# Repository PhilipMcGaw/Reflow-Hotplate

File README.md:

# reflow_hotplate
 SMD reflow hot plate

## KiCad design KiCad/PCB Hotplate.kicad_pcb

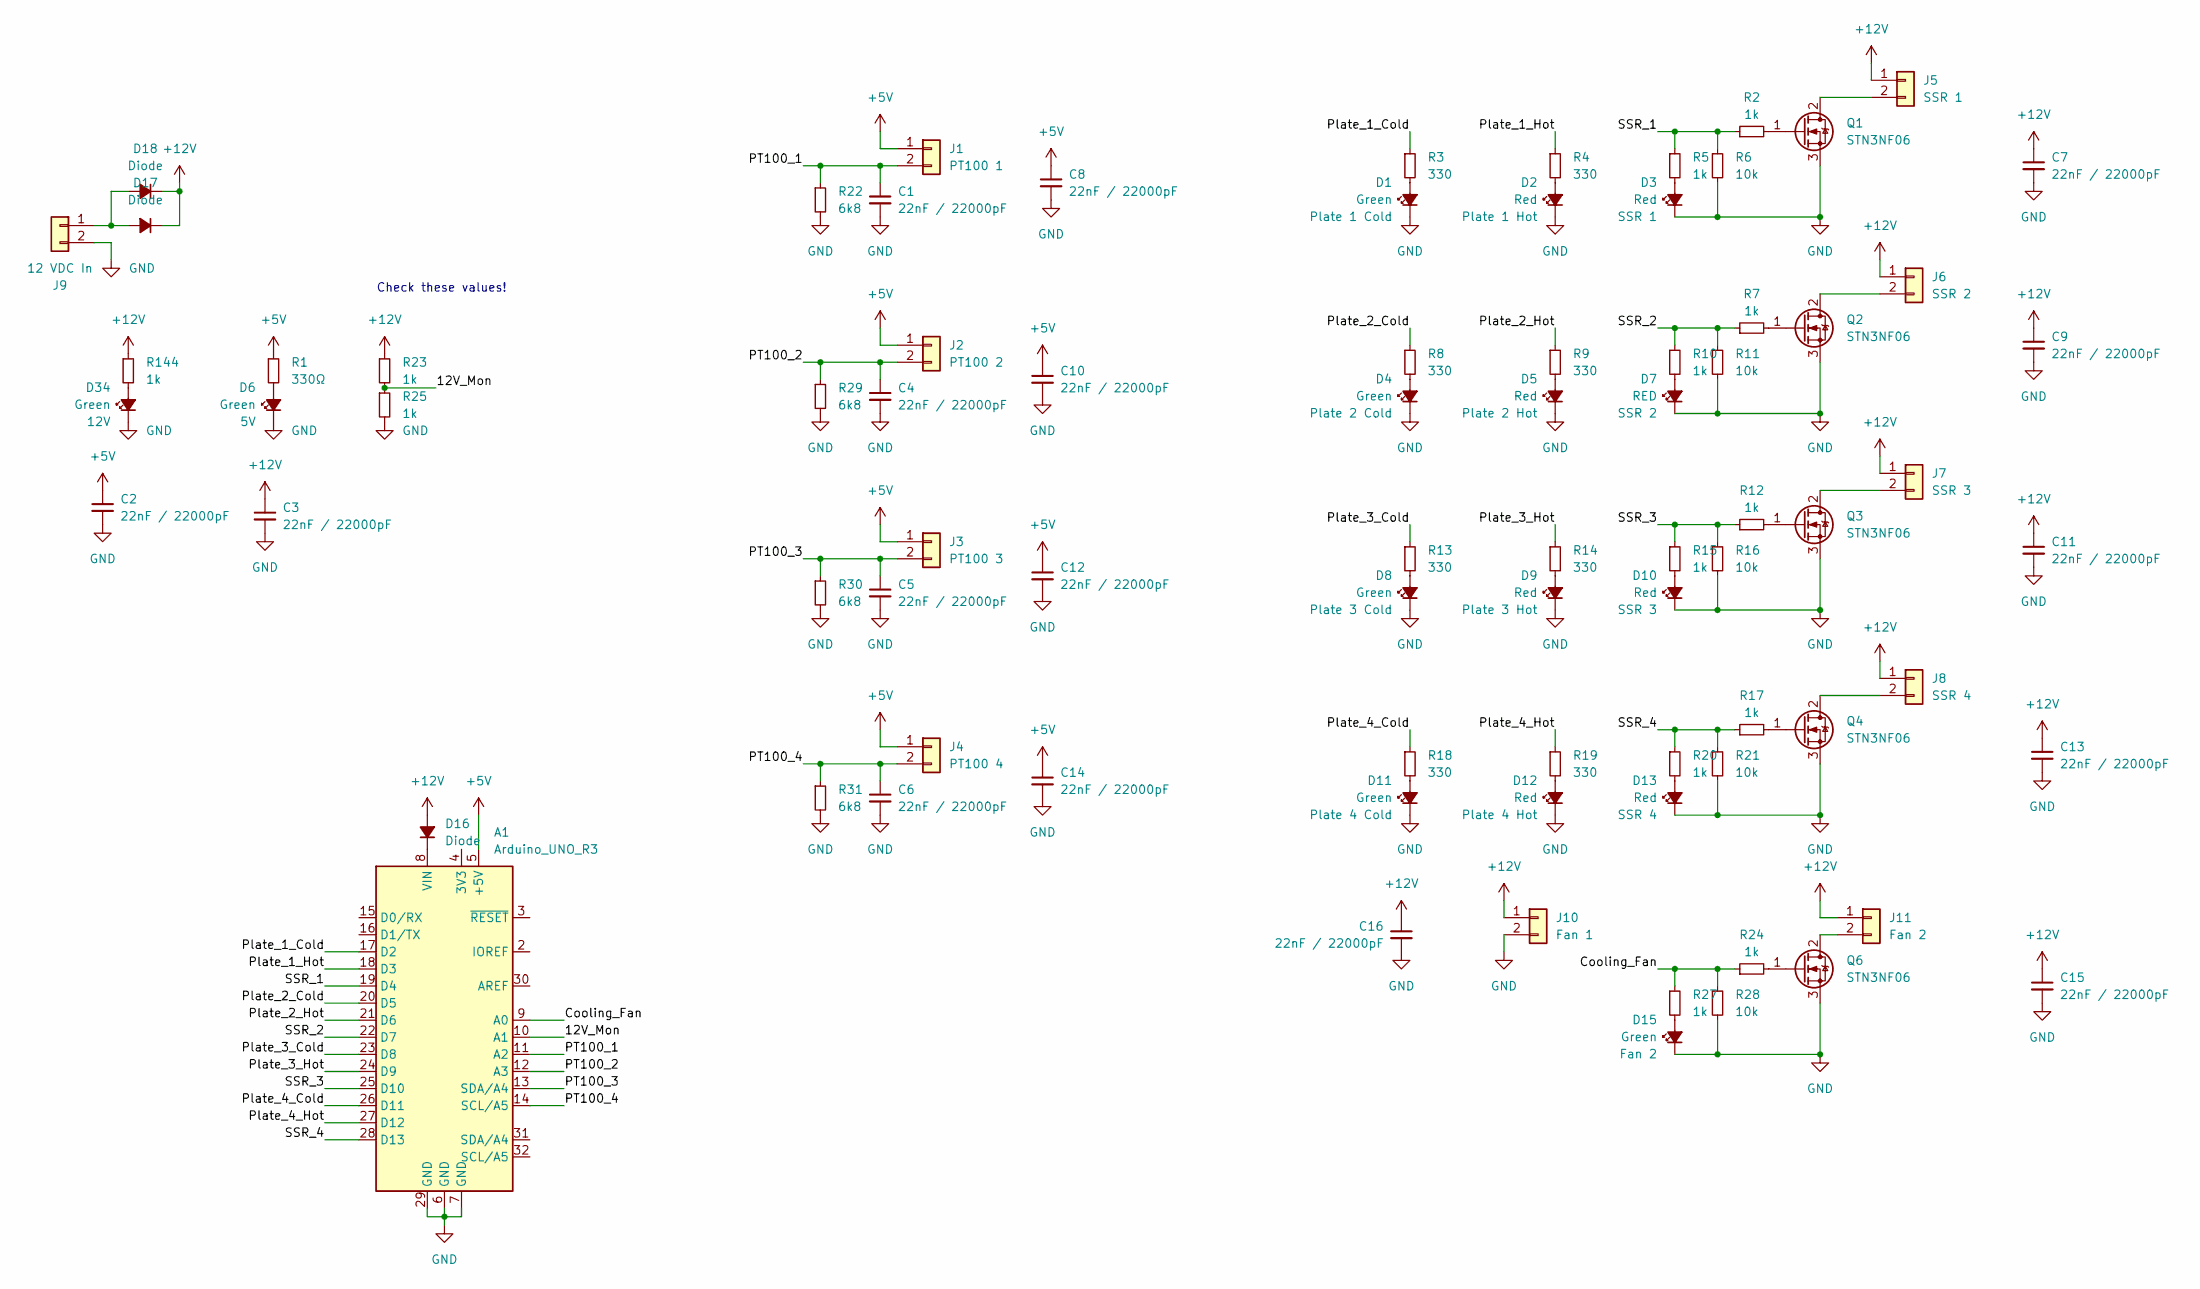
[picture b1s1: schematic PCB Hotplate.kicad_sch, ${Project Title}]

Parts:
A1: Arduino_UNO_R3
C1, C2, C3, C4, C5, C6, C7, C8, C9, C10, C11, C12, C13, C14, C15, C16: 22nF / 22000pF; C_0805_2012Metric_Pad1.18x1.45mm_HandSolder; Manufacturer Part Number 885012207041; Farnell Partnumber 2812402
D1, D4, D6, D8, D11, D34: Green; LED_0805_2012Metric_Pad1.15x1.40mm_HandSolder; Farnell Partnumber 3796308
D2, D5, D9, D12: Red; LED_0805_2012Metric_Pad1.15x1.40mm_HandSolder; Farnell Partnumber 3796308
D3, D10, D13: Red; LED_0805_2012Metric_Pad1.15x1.40mm_HandSolder; Farnell Partnumber 3796325
D7: RED; LED_0805_2012Metric_Pad1.15x1.40mm_HandSolder; Farnell Partnumber 3796325
D15: Green; LED_0805_2012Metric_Pad1.15x1.40mm_HandSolder; Farnell Partnumber 3796325
D16, D17, D18: Diode; D_SMA
J1: PT100 1; TerminalBlock_TE_282834-2_1x02_P2.54mm_Horizontal
J2: PT100 2; TerminalBlock_TE_282834-2_1x02_P2.54mm_Horizontal
J3: PT100 3; TerminalBlock_TE_282834-2_1x02_P2.54mm_Horizontal
J4: PT100 4; TerminalBlock_TE_282834-2_1x02_P2.54mm_Horizontal
J5: SSR 1; TerminalBlock_TE_282834-2_1x02_P2.54mm_Horizontal
J6: SSR 2; TerminalBlock_TE_282834-2_1x02_P2.54mm_Horizontal
J7: SSR 3; TerminalBlock_TE_282834-2_1x02_P2.54mm_Horizontal
J8: SSR 4; TerminalBlock_TE_282834-2_1x02_P2.54mm_Horizontal
J9: 12 VDC In; TerminalBlock_TE_282834-2_1x02_P2.54mm_Horizontal
J10: Fan 1; TerminalBlock_TE_282834-2_1x02_P2.54mm_Horizontal
J11: Fan 2; TerminalBlock_TE_282834-2_1x02_P2.54mm_Horizontal
Q1, Q2, Q3, Q4, Q6: STN3NF06; SOT-223-3_TabPin2; Farnell Partnumber 1752120
R1: 330Ω; R_0805_2012Metric_Pad1.20x1.40mm_HandSolder
R2, R5, R7, R10, R12, R15, R17, R20, R23, R24, R25, R27, R144: 1k; R_0805_2012Metric_Pad1.20x1.40mm_HandSolder
R3, R4, R8, R9, R13, R14, R18, R19: 330; R_0805_2012Metric_Pad1.20x1.40mm_HandSolder
R6, R11, R16, R21, R28: 10k; R_0805_2012Metric_Pad1.20x1.40mm_HandSolder
R22, R29, R30, R31: 6k8; R_0805_2012Metric_Pad1.20x1.40mm_HandSolder

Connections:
+5V: A1.5 (+5V), C2.1, C8.1, C10.1, C12.1, C14.1, J1.1, J2.1, J3.1, J4.1, R1.1
+12V: C3.1, C7.1, C9.1, C11.1, C13.1, C15.1, C16.1, D16.2 (A), D17.1 (K), D18.1 (K), J5.1, J6.1, J7.1, J8.1, J10.1, J11.1, R23.1, R144.1
/12V_Mon: A1.10 (A1), R23.2, R25.1
/Cooling_Fan: A1.9 (A0), R24.1, R27.1, R28.1
/PT100_1: A1.11 (A2), C1.1, J1.2, R22.1
/PT100_2: A1.12 (A3), C4.1, J2.2, R29.1
/PT100_3: A1.13 (SDA/A4), C5.1, J3.2, R30.1
/PT100_4: A1.14 (SCL/A5), C6.1, J4.2, R31.1
/Plate_1_Cold: A1.17 (D2), R3.1
/Plate_1_Hot: A1.18 (D3), R4.1
/Plate_2_Cold: A1.20 (D5), R8.1
/Plate_2_Hot: A1.21 (D6), R9.1
/Plate_3_Cold: A1.23 (D8), R13.1
/Plate_3_Hot: A1.24 (D9), R14.1
/Plate_4_Cold: A1.26 (D11), R18.1
/Plate_4_Hot: A1.27 (D12), R19.1
/SSR_1: A1.19 (D4), R2.1, R5.1, R6.1
/SSR_2: A1.22 (D7), R7.1, R10.1, R11.1
/SSR_3: A1.25 (D10), R12.1, R15.1, R16.1
/SSR_4: A1.28 (D13), R17.1, R20.1, R21.1
GND: A1.6 (GND), A1.7 (GND), A1.29 (GND), C1.2, C2.2, C3.2, C4.2, C5.2, C6.2, C7.2, C8.2, C9.2, C10.2, C11.2, C12.2, C13.2, C14.2, C15.2, C16.2, D1.1 (K), D2.1 (K), D3.1 (K), D4.1 (K), D5.1 (K), D6.1 (K), D7.1 (K), D8.1 (K), D9.1 (K), D10.1 (K), D11.1 (K), D12.1 (K), D13.1 (K), D15.1 (K), D34.1 (K), J9.2, J10.2, Q1.3 (S), Q2.3 (S), Q3.3 (S), Q4.3 (S), Q6.3 (S), R6.2, R11.2, R16.2, R21.2, R22.2, R25.2, R28.2, R29.2, R30.2, R31.2
unnamed: A1.8 (VIN), D16.1 (K)
unnamed: D1.2 (A), R3.2
unnamed: D2.2 (A), R4.2
unnamed: D3.2 (A), R5.2
unnamed: D4.2 (A), R8.2
unnamed: D5.2 (A), R9.2
unnamed: D6.2 (A), R1.2
unnamed: D7.2 (A), R10.2
unnamed: D8.2 (A), R13.2
unnamed: D9.2 (A), R14.2
unnamed: D10.2 (A), R15.2
unnamed: D11.2 (A), R18.2
unnamed: D12.2 (A), R19.2
unnamed: D13.2 (A), R20.2
unnamed: D15.2 (A), R27.2
unnamed: D17.2 (A), D18.2 (A), J9.1
unnamed: D34.2 (A), R144.2
unnamed: J5.2, Q1.2 (D)
unnamed: J6.2, Q2.2 (D)
unnamed: J7.2, Q3.2 (D)
unnamed: J8.2, Q4.2 (D)
unnamed: J11.2, Q6.2 (D)
unnamed: Q1.1 (G), R2.2
unnamed: Q2.1 (G), R7.2
unnamed: Q3.1 (G), R12.2
unnamed: Q4.1 (G), R17.2
unnamed: Q6.1 (G), R24.2

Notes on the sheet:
Check these values!

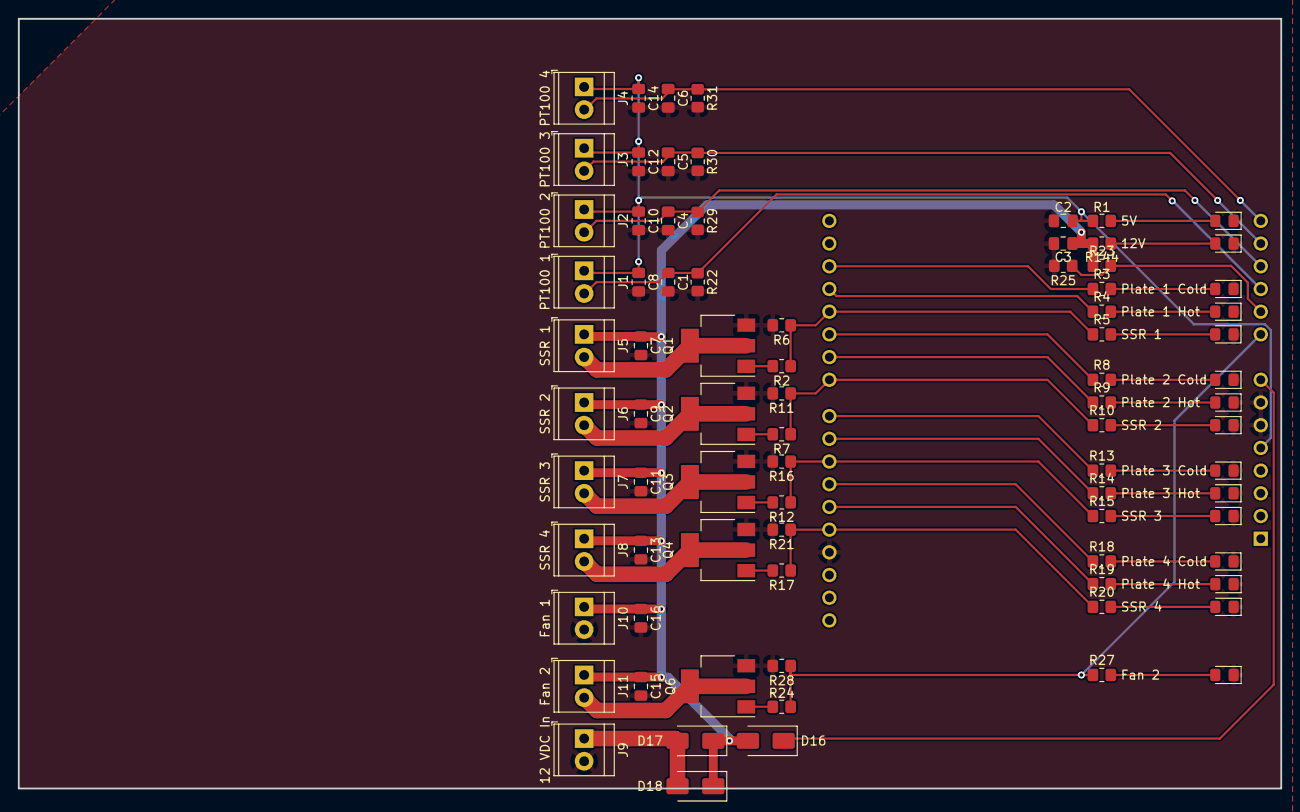
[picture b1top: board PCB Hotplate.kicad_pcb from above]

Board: 2 copper layers, 141.2 x 86.1 mm, 82 parts (1 on the bottom side), 48 nets.

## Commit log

2023-12-13 Started
